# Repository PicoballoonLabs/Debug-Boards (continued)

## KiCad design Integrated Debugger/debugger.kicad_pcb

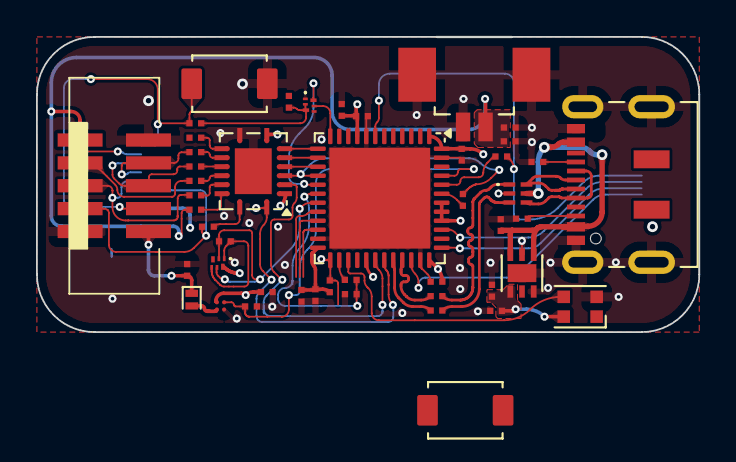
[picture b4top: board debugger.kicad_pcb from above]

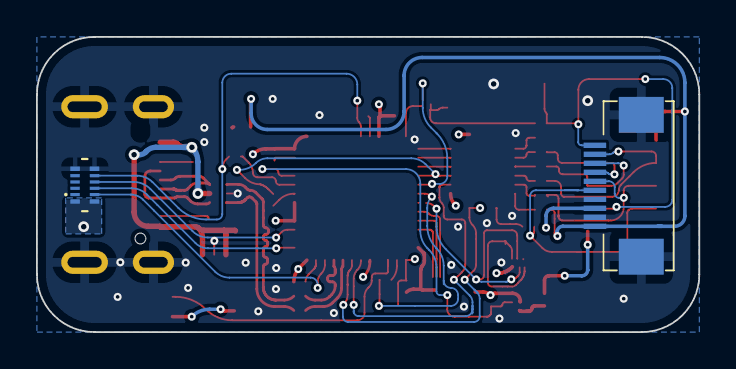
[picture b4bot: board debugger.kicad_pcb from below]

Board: 4 copper layers, 36.8 x 16.4 mm, 49 parts (2 on the bottom side), 50 nets.

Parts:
C1, C2, C8, C11: 1μF; Capacitor 0201
C3, C4, C5, C6, C7, C10, C12, C13, C14: 100nF; Capacitor 0201
C9: 4.7μF; Capacitor 0201
D2: WS2812B-2020
D6: PMEG3005EL,315; Diode SOD-882
J1: B2B GT-B0353FSV06-08B0201; B2B GT-B0353MSV04-08B0201
J2: USB_C (PC <-> Host); USB-C DX07S016JA1R1500
J3: FPC socket 10P; FPC connector FPC-05F-10PH20
J4: 20021521-00010T1LF
J5: PWR; MOLEX 532610271
Q1: NMOS DMN2991UDA-7B; X2-DFN0806-6
Q2: PMOS DMP32D9UDA-7B; X2-DFN0806-6
R1, R13, R15, R16, R17: 10kΩ; Resistor 0201
R2, R3: 22Ω; Resistor 0201
R4, R5, R6, R7, R8, R9, R10, R18: 100Ω; Resistor 0201
R11, R12: 1.5kΩ; Resistor 0201
R14: 4.7kΩ; Resistor 0201
R19: 0Ω; Resistor 0201
SW1: RESET; Button GT-TC029B-H025-L1N
SW2: BOOT; Button GT-TC029B-H025-L1N
U1: TPS7A2633DRVR; WSON-6 2x2mm
U2: USBULC6-2M6; UQFN-6
U3: STM32F103CBUx; QFN-48-1EP_7x7mm_P0.5mm_EP5.6x5.6mm
U4: TXB0106RGY; Texas_RGY_R-PVQFN-N16_EP2.05x2.55mm
U8: TPS22914; DSBGA-4

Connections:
+3.3V: C2.1, C4.2, C5.2, C6.2, C7.2, C8.2, C9.2, C12.1, D2.4 (VDD), J1.P1 (Pin_9), J1.P1_2 (Pin_9), Q2.6, R13.1, U1.1 (OUT), U3.1 (VBAT), U3.9 (VDDA), U3.24 (VDD), U3.36 (VDD), U3.40 (PB4), U3.41 (PB5), U3.42 (PB6), U3.48 (VDD), U4.2 (V_{CCA}), U4.8 (OE)
+5V: C1.1, J2.A4 (VBUS), J2.A9 (VBUS), J2.B4 (VBUS), J2.B9 (VBUS), U1.4 (EN), U1.6 (IN), U2.5 (VBUS)
/D+: J2.A6 (D+), J2.B6 (D+), U2.6 (I/O1)
/D-: J2.A7 (D-), J2.B7 (D-), U2.4 (I/O2)
/MCU/LEDX: D2.3 (DIN), U3.27 (PB14)
/MCU/SOL_EN: R1.1, U3.45 (PB8), U8.B2 (ON)
/MCU/SWD.CLK: J1.4, U3.37 (PA14)
/MCU/SWD.IO: J1.2, U3.34 (PA13)
/MCU/TARGET_EN: Q2.2, Q2.5, R17.1, U3.19 (PB1)
/MCU/TRACESWO: J1.6, U3.39 (PB3)
/MCU/USB.D+: R3.1, U3.33 (PA12)
/MCU/USB.D-: R2.1, U3.32 (PA11)
/MCU/VBUS: R14.1, U3.26 (PB13)
/MCU/i.RST: Q1.5, U3.12 (PA2)
/MCU/i.RST_SEN: Q1.6, U3.17 (PA7)
/MCU/i.RX: U3.31 (PA10), U4.1 (A1)
/MCU/i.TCK: U3.15 (PA5), U4.5 (A4)
/MCU/i.TDI: U3.13 (PA3), U4.7 (A6)
/MCU/i.TDO: R19.2, U3.16 (PA6), U4.4 (A3)
/MCU/i.TMS: U3.14 (PA4), U4.6 (A5)
/MCU/i.TX: U3.30 (PA9), U4.3 (A2)
/MCU/~RST: C3.2, J1.8, U3.7 (NRST)
/Power/V_SOLAR_UNFILT: D6.2 (A), U8.A1 (VOUT)
/Target Frontend/xRST: Q1.2, Q1.3, R4.1, R16.2
/Target Frontend/xRXD: R6.1, U4.16 (B1)
/Target Frontend/xTCK: R10.1, U4.12 (B4)
/Target Frontend/xTDI: R7.1, U4.10 (B6)
/Target Frontend/xTDO: R9.1, U4.13 (B3)
/Target Frontend/xTMS: R5.1, U4.11 (B5)
/Target Frontend/xTXD: R8.1, U4.14 (B2)
/Target/tRST: J3.10, J4.8 (RST), R4.2, SW1.2 (B)
/Target/tRXD: J3.5, J4.7 (TG_TX), R6.2
/Target/tTCK: J3.8, J4.6 (SWDCLK), R10.2
/Target/tTDO: J3.9, J4.3 (SWO), R9.2
/Target/tTMS: J3.7, J4.4 (SWDIO), R5.2
/Target/tTXD: J3.6, J4.5 (TG_RX), R8.2
/USBX.D+: R3.2, U2.1 (I/O1)
/USBX.D-: R2.2, U2.3 (I/O2)
GND: C1.2, C2.2, C4.1, C5.1, C6.1, C7.1, C8.1, C9.1, C10.2, C11.2, C12.2, C13.2, C14.2, D2.2 (VSS), J1.P2 (Pin_10), J1.P2_2 (Pin_10), J2.A1 (GND), J2.A12 (GND), J2.B1 (GND), J2.B12 (GND), J2.S1 (SHIELD), J3.2, J3.4, J3.S1, J3.S2, J4.2 (GND), J4.9 (GND), J5.2, J5.S1, J5.S2, Q1.1, Q1.4, R1.2, R11.2, R12.2, R15.2, SW1.1 (A), SW2.1 (A), U1.3 (PG), U1.5 (GND), U1.7 (EXP), U2.2 (GND), U3.8 (VSSA), U3.23 (VSS), U3.35 (VSS), U3.47 (VSS), U3.49 (VSS), U4.9 (GND), U4.17 (GND), U8.B1 (GND)
unnamed: J2.A5 (CC1), R11.1
unnamed: J2.B5 (CC2), R12.1
unnamed: Q2.1, Q2.4, R17.2
unnamed: R13.2, SW2.2 (B), U3.25 (PB12)
unnamed: C3.1, U3.44 (BOOT0)
unnamed: R14.2, R15.1, U3.18 (PB0)
unnamed: R19.1, U3.43 (PB7)
V_SOLAR: C14.1, D6.1 (K), J3.3, J4.10 (SOLAR)
V_TARGET: C10.1, C11.1, J3.1, J4.1 (VCC), J5.1, Q2.3, R18.1
V_USB: C13.1, U8.A2 (VIN)
xTPWR: R18.2, U4.15 (V_{CCB})

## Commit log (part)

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2025-08-11 Add Probe adapter and flex debug cable
2025-08-11 Fix name
2025-08-11 Ignore lockfiles
2025-08-12 Design flex debug cable V1.1
2025-08-18 feat: add integrated debugger
2025-08-20 feat: wip board layout and routing
2025-08-22 feat: finish majority of routing
2025-08-23 feat: finish routing of components
2025-08-23 feat: add manufacturing data
2025-08-24 Revise schematic, add worksheet libraries
2025-08-24 Schematic consistency improvements
2025-08-24 PCB improvements
2025-08-25 feat: debugger flip swd connector, usb patch + stackup change
2025-08-25 Improve routing, placement & decorations, final check pass
2025-08-25 fix: usb fs diff pair routing
2025-08-25 Update BOM
2025-08-25 Update SN position
2025-09-10 feat: swap debugger rgb led part
2025-09-10 feat: change debugger part mnf data
2025-09-10 Change diode
2025-11-01 Debug cable production files
2025-11-01 feat: fix debugger bugs & impl. auxiliary power - 869b0p9f3
2025-11-01 chore: debugger add mosfet mfr details
2025-11-01 Prepare for production
2025-11-03 fix(debugger): relpace picostar 0.4 with 0.65 variant
2025-11-04 Debugger 1.1.2 production files
2025-11-04 Update assembly
2025-11-05 Update component models
2025-12-10 VNA-RF calibration board created
2025-12-23 Cleanup & standardize schematic & PCB
2025-12-23 Finish VNA calibration board, production files
2026-03-26 IDBG schematic
2026-03-27 Integrated debugger PCB
2026-03-30 Reannotate schematic, update GND plane
2026-03-30 led+ resistors updated
2026-03-30 capacitors updated
2026-03-30 Fix 3D models, add approvals
2026-03-31 IDBG v2.0 production files
